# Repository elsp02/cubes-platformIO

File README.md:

# Modular Mechatronic Smart-Brick System for Tangible Learning in Special Education
Repository accompanying the Bachelor thesis:

**Design and Development of a Tangible Learning System for Special Education**

Elena Spitzer  
University of Applied Sciences Augsburg  
Faculty of Electrical Engineering  
Creative Engineering  
2026  

## Overview
This repository contains the prototype developed as part of the Bachelor thesis and investigates a modular, brick-based tangible learning game that combines the haptic and spatial qualities of physical construction materials with digital task presentation, construction detection and feedback. Learners select a three-dimensional target structure in a browser-based application and reproduce it using electronically connected building bricks. The system was designed to create opportunities for spatial thinking, action planning, problem-solving and increasingly independent learning while allowing task complexity and assistance to be adapted to individual needs. 

The system consists of three main components:

- **Active building bricks** that form the physical construction
- **A baseplate** that serves as the root of the construction
- **A learning application** that reconstructs the detected construction digitally

<center>

</center>

## Repository Structure

```text
.
├── README.md
│
├── docs/
│   ├── architecture.md
│   ├── communication-protocol.md
│   ├── feedback.md
│   ├── hardware.md
│   ├── language_c.md
│
├── figures/
│
├── firmware/
│   ├── include/
│   └── src/
│        ├── lib/
│        ├── firmware_test/
│        └── state_machine/
│         ├── baseplate_state_machine_debug.cpp
│         ├── baseplate_state_machine2.cpp
│         └── cube_state_machine.cpp
│
├── software/
│   └── threejs_visualization/
│     ├── backend/
│     └── frontend/
│
└── hardware/
    ├── pcb_files/
    └── CAD_files/

```

|Directory | Description |
|:--|:--|
| `docs/` | Technical documentation of the developed system |
| `firmware/` | Embedded firmware for the building bricks and the baseplate |
| `software/threejs_visualization/backend` | Python backend for communication and construction processing |
| `software/threejs_visualization/frontend` | Browser-based learning application and 3D visualisation |
| `hardware` | Electronic and mechanical design files

## Documentation
Detailed technical documentation is provided separately: 
- [System Architecuture](docs/system_architecture.md): Overall system structure, component responsibilities, software architecture and data processing
- [Communication Protocol](docs/communication_protocol.md): Communication interfaces, message formats, communication sequences (and error and timeout handling)
- [Hardware](docs/hardware.md): Mechanical and electronic implementation of the building bricks and baseplate

Addtional information regarding the feedback output and visualisation is provided in [Feedback and Visualisation](docs/feedback.md).

Firmware and Software Folders do also have additional README files [Firmware README](firmware/README.md), [Software README](software/README.md), as well as the backend [backend README](software/threejs_visualization/backend/README.md) 
and the frontend [frontend README](software/threejs_visualization/frontend/README.md)

(Furthermore, the bachelor thesis includes the complete design rationale, theoretical background, requirement analysis, implementation details and evaluation.)

## Requirements
to operate the complete physical prototype, the following hard- and software is required:

### Prototype Hardware
The building bricks and baseplate both include an ATtiny1616 and are custom developed components. Their mechanical and electronic design files are included in this repository in the [hardware](hardware/) and explained in [Hardware](docs/hardware.md)

### Additional Hardware
- 2× USB-to-TTL UART adapter (CH340/CH340G-based)
  - one modified with a TX/RX diode, used as UPDI programmer (jtag2updi)
  - one unmodified, used for host–baseplate UART communication and 5V supply
- host computer
- USB connection for 5V power supply

The prototype was programmed using the jtag2updi-compatible programmer.
Setup instructions are available in the
[jtag2updi documentation](https://github.com/SpenceKonde/AVR-Guidance/blob/master/UPDI/jtag2updi.md).

### Software
- [PlatformIO](https://platformio.org/)
- [megaTinyCore](https://github.com/SpenceKonde/megaTinyCore) for ATtiny1616 support
- Python 3.14
- modern web browser

**Python dependencies**:  
- `pyserial` (UART communication, [binary_serial_reader.py](software/threejs_visualization/backend/binary_serial_reader.py))
- `websockets` (backend WebSocket server, [ws_server.py](software/threejs_visualization/backend/ws_server.py))

Python dependencies can be installed via:  
```bash
pip install -r software/threejs_visualization/backend/requirements_backend.txt
```

**Frontend dependencies** (in [software/threejs_visualization/frontend/package.json](software/threejs_visualization/frontend/package.json)):  
- `three` (^0.185.1)  
- `vite` (^8.1.2) — dev server / bundler

Install with:  
```bash
cd software/threejs_visualization/frontend
npm install
```

## Getting Started
### 1. Clone the Repository
git `clone https://github.com/elsp02/cubes-platformIO.git`  
cd cubes-platformIO

### 2. Flash the Brick and Baseplate Firmware
for flashing use the modified USB-to-TTL UART adapter

#### Brick Firmware
the brick firmware is located in: [firmware/src/state_machine]  
Compile the firmware and upload the ATtiny1616 using PlatformIO:  
```bash
pio run -e [uart_cube_state_machine]
```

```bash
pio run -e [uart_cube_state_machine] -t upload
```
---
#### Baseplate Firmware
the baseplate firmware is located in: [firmware/src/state_machine]

Compile the firmware and upload the ATtiny1616 using PlatformIO: 
```bash
pio run -e [uart_baseplate_state_machine]
```

```bash
pio run -e [uart_baseplate_state_machine] -t upload
```
---
#### Debugging
 to run the baseplate standalone without a PC connection, cycling the predefined feedback patterns instead of PC-supplied data, flash the `[baseplate_state_machine_debug]` environment instead:
 ```bash
 pio run -e [baseplate_state_machine_debug]
 ```

### 3. Connect the Prototype
1. Connect the baseplate to the host computer using the unmodified USB-to-TTL UART adapter
2. ensure that the system is supplied with 5V
3. Do not connect bricks to the baseplate yet
For details about the physical and electronic interfaces, see the [Hardware Documentation](docs/hardware.md)

### 4. Start the Backend
Navigate to the backend directory:  
```bash
cd software/threejs_visualization/backend
```
Start the backend:
```bash
python ws_server.py
```

### 5. Start the Frontend
Navigate to the frontend directory:
```bash
cd software/threejs_visualization/frontend
```
Start the frontend and open it in a web browser:
```bash
npm run dev
```

## Usage
A typical construction task follows this sequence:
1. Start the backend and frontend
2. Select a target construction in the learning application
3. Inspect and confirm the selected three-dimensional target
4. Connect the first brick to the baseplate.
5. Continue the building process by trying to reproduce the target structure 
5. The system processes the current construction and updates the digital representation.
6. Rearrange a brick if it is detected and visualised as incorrect
7. Continue modifying the construction until the task is completed
8. End the current session or return to the target selection

The visualised feedback during the construction task inlcuding pyhsical and digital feedback and feedback states is explained in detail in the[Feedback Documentation](docs/feedback.md).

## Prototype Status
//baseplate flashed currently with uart_baseplate_sate_machine env of commit 9cc54fb7
//cube flashed currently with uart_cube_state_machine env of commit 05d4e983

This repository contains the proof-of-concept prototype developed for the Bachelor thesis. It is not a production-ready or certified educational product.

Further information about the evaluation, requirement fulfilment and limitations is provided in the Bachelor thesis.

## Version
The version associated with the submitted Bachelor thesis is:
Tag:    [prototype_v11_final]  
Commit: [FINAL_COMMIT]  

Later commits may contain modifications that are not described in the submitted thesis.

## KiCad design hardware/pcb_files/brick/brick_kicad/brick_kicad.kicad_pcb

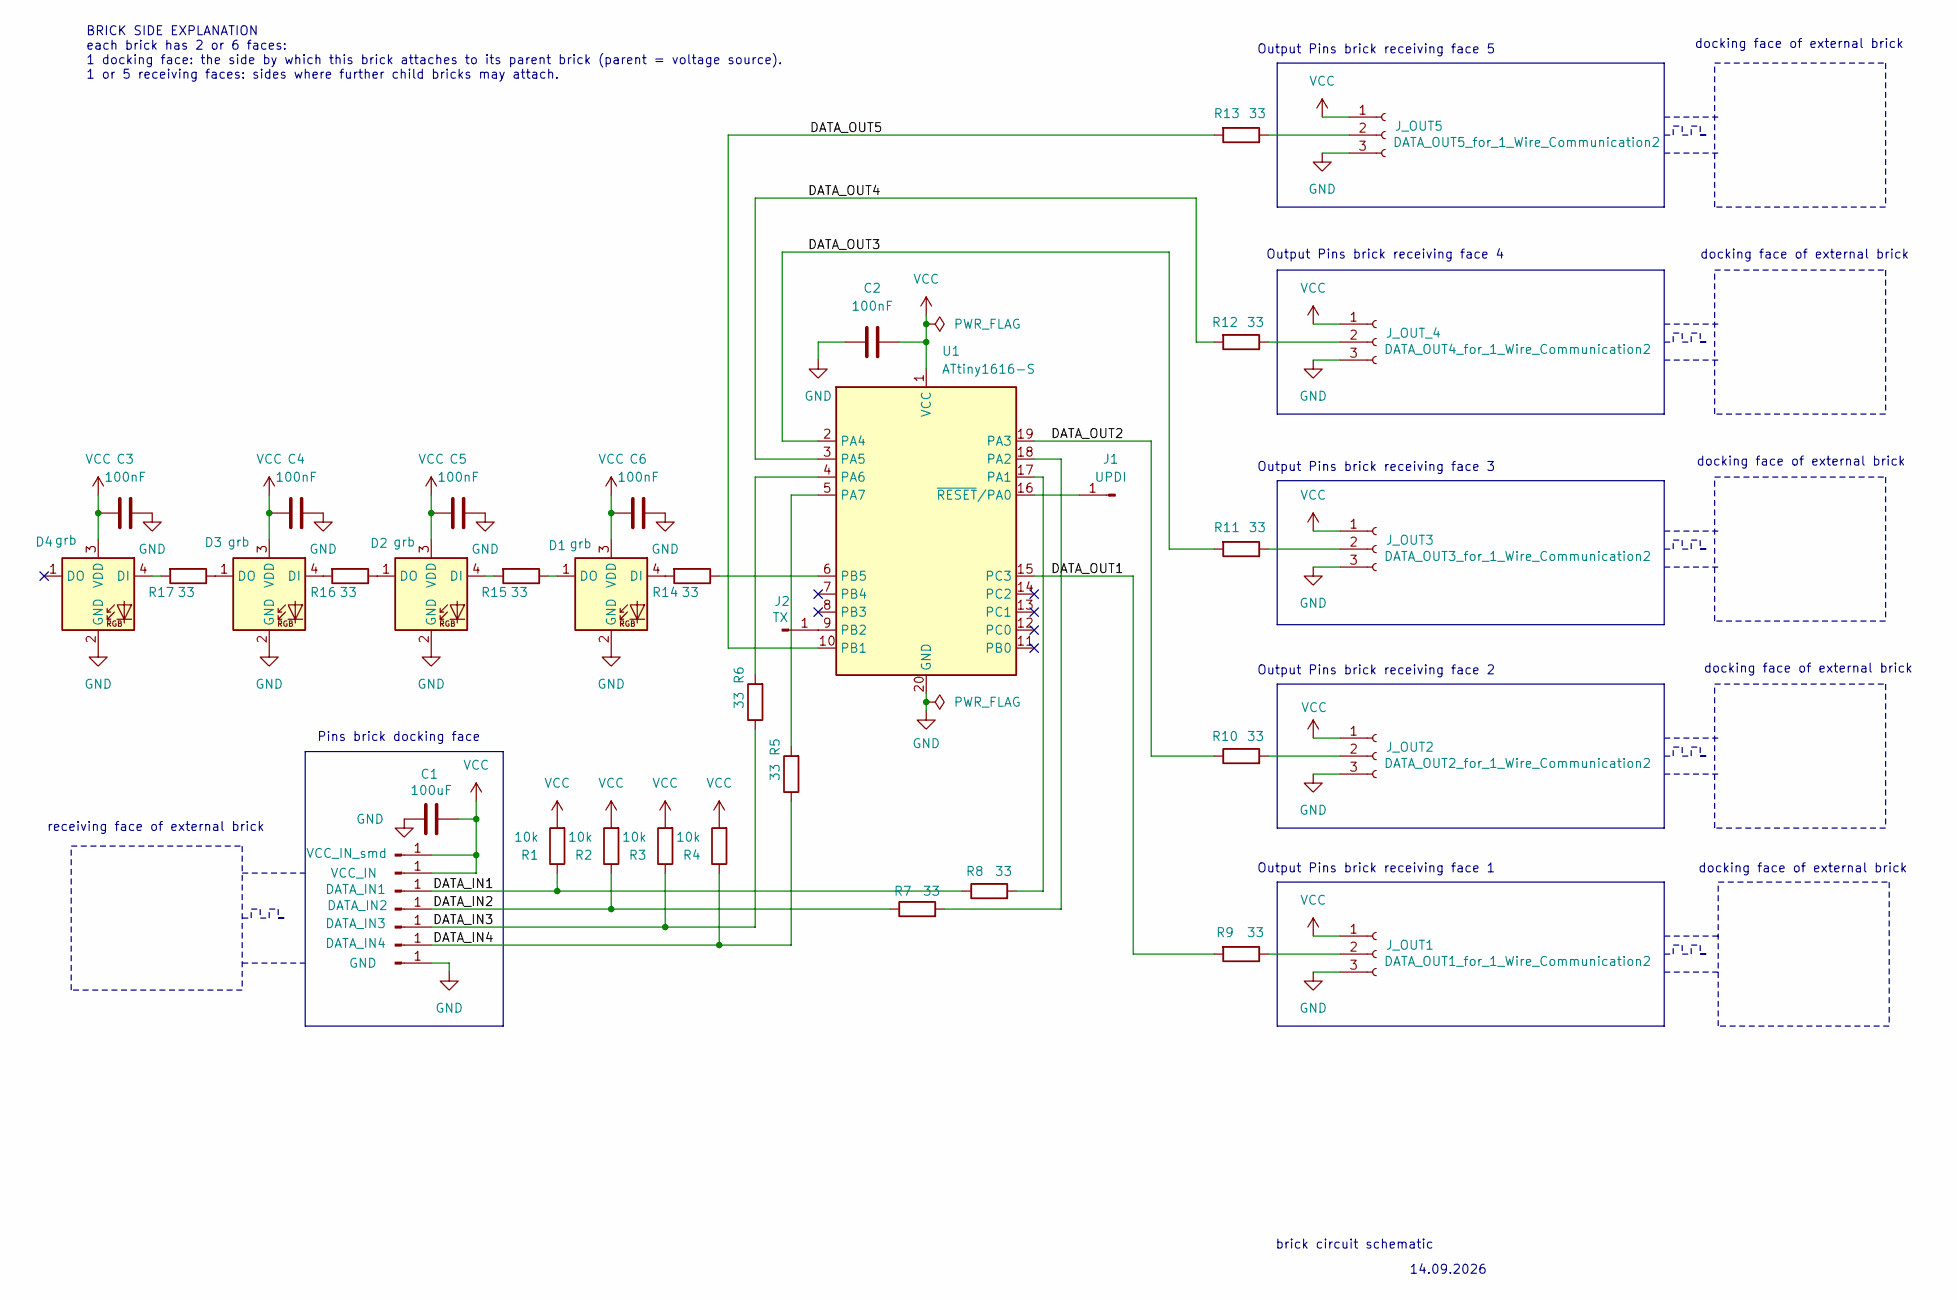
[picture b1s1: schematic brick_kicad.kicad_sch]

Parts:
C1: 100uF; C_1206_3216Metric_Pad1.33x1.80mm_HandSolder; MPN 885012108005
C2, C3, C4, C5, C6: 100nF; C_0805_2012Metric_Pad1.18x1.45mm_HandSolder; MPN 885012207016
D1, D2, D3, D4: grb; U_Wurth_WL-ICLED_1313210530000
J1: UPDI; PinSocket_1x01_P2.54mm_Vertical
J2: TX; PinSocket_1x01_P2.54mm_Vertical
J_GND1: GND; pogo_pad_IN
J_IN1: DATA_IN1; pogo_pad_IN
J_IN2: DATA_IN2; pogo_pad_IN
J_IN3: DATA_IN3; pogo_pad_IN
J_IN4: DATA_IN4; pogo_pad_IN
J_OUT1: DATA_OUT1_for_1_Wire_Communication2; Wuerth_WR-WTB_64800311622_1x03_P1.50mm_Vertical; MPN 64800311622
J_OUT2: DATA_OUT2_for_1_Wire_Communication2; Wuerth_WR-WTB_64800311622_1x03_P1.50mm_Vertical; MPN 64800311622
J_OUT3: DATA_OUT3_for_1_Wire_Communication2; Wuerth_WR-WTB_64800311622_1x03_P1.50mm_Vertical; MPN 64800311622
J_OUT5: DATA_OUT5_for_1_Wire_Communication2; Wuerth_WR-WTB_64800311622_1x03_P1.50mm_Vertical; MPN 64800311622
J_OUT_4: DATA_OUT4_for_1_Wire_Communication2; Wuerth_WR-WTB_64800311622_1x03_P1.50mm_Vertical; MPN 64800311622
J_VCC1: VCC_IN; pogo_pin_magnet
J_VCC2: VCC_IN_smd; pogo_pin_smd
R1, R2, R3, R4: 10k; R_0603_1608Metric_Pad0.98x0.95mm_HandSolder; MPN 560112116005
R5, R6, R7, R8, R9, R10, R11, R12, R13, R14, R15, R16, R17: 33; R_0603_1608Metric_Pad0.98x0.95mm_HandSolder; MPN 560112116034
U1: ATtiny1616-S; SOIC-20W_7.5x12.8mm_P1.27mm

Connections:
/DATA_IN1: J_IN1.1 (Pin_1_1), R1.1, R8.1
/DATA_IN2: J_IN2.1 (Pin_1_1), R2.1, R7.1
/DATA_IN3: J_IN3.1 (Pin_1_1), R3.1, R6.1
/DATA_IN4: J_IN4.1 (Pin_1_1), R4.1, R5.1
/DATA_OUT1: R9.2, U1.15 (PC3)
/DATA_OUT2: R10.1, U1.19 (PA3)
/DATA_OUT3: R11.2, U1.2 (PA4)
/DATA_OUT4: R12.2, U1.3 (PA5)
/DATA_OUT5: R13.2, U1.10 (PB1)
GND: C1.1, C2.2, C3.1, C4.1, C5.1, C6.1, D1.2 (GND), D2.2 (GND), D3.2 (GND), D4.2 (GND), J_GND1.1 (Pin_1_1), J_OUT1.3, J_OUT2.3, J_OUT3.3, J_OUT5.3, J_OUT_4.3, U1.20 (GND)
unnamed: D1.4 (DI), R14.2
unnamed: D1.1 (DO), R15.1
unnamed: D2.4 (DI), R15.2
unnamed: D2.1 (DO), R16.1
unnamed: D3.4 (DI), R16.2
unnamed: D3.1 (DO), R17.1
unnamed: D4.4 (DI), R17.2
unnamed: J1.1 (Pin_1_1), U1.16 (~RESET/PA0)
unnamed: J2.1 (Pin_1_1), U1.9 (PB2)
unnamed: J_OUT1.2, R9.1
unnamed: J_OUT2.2, R10.2
unnamed: J_OUT3.2, R11.1
unnamed: J_OUT5.2, R13.1
unnamed: J_OUT_4.2, R12.1
unnamed: R8.2, U1.17 (PA1)
unnamed: R7.2, U1.18 (PA2)
unnamed: R6.2, U1.4 (PA6)
unnamed: R5.2, U1.5 (PA7)
unnamed: R14.1, U1.6 (PB5)
VCC: C1.2, C2.1, C3.2, C4.2, C5.2, C6.2, D1.3 (VDD), D2.3 (VDD), D3.3 (VDD), D4.3 (VDD), J_OUT1.1, J_OUT2.1, J_OUT3.1, J_OUT5.1, J_OUT_4.1, J_VCC1.1 (Pin_1_1), J_VCC2.1 (Pin_1_1), R1.2, R2.2, R3.2, R4.2, U1.1 (VCC)

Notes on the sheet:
Output Pins brick receiving face 3
docking face of external brick
BRICK SIDE EXPLANATION each brick has 2 or 6 faces: 1 docking face: the side by which this brick attaches to its parent brick (parent = voltage source). 1 or 5 receiving faces: sides where further child bricks may attach.
14.09.2026
Output Pins brick receiving face 4
Output Pins brick receiving face 2
Output Pins brick receiving face 5
receiving face of external brick
Pins brick docking face
brick circuit schematic
Output Pins brick receiving face 1

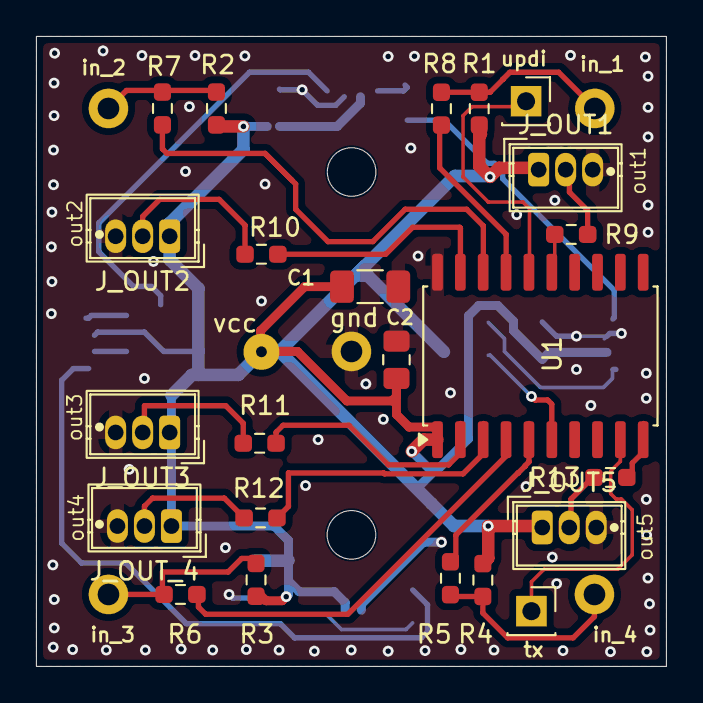
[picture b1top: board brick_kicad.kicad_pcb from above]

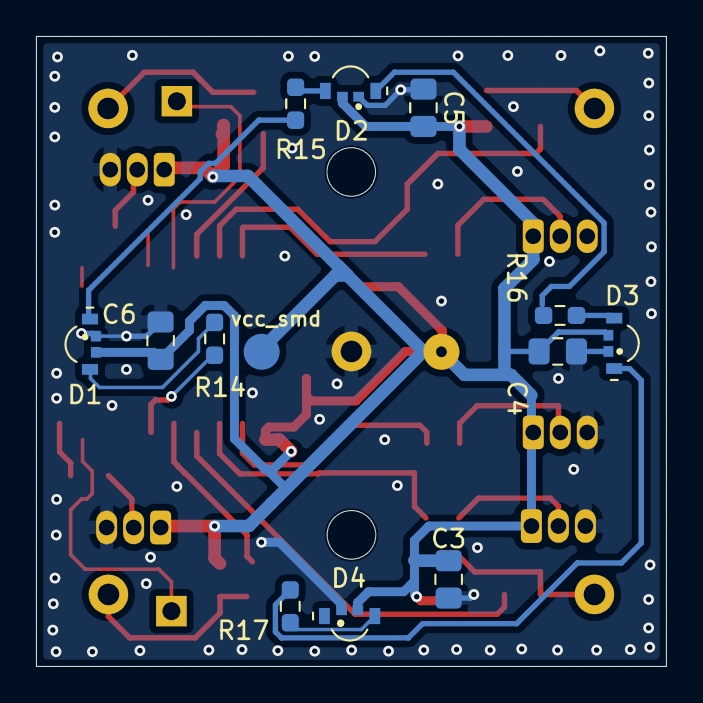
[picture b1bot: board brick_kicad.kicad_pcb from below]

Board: 2 copper layers, 35.0 x 35.0 mm, 42 parts (13 on the bottom side), 30 nets.

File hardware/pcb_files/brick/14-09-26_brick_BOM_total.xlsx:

Reference | Qty | Value | Footprint | Datasheet | Notes
C1 | 1 | 100uF | Capacitor_SMD:C_1206_3216Metric_Pad1.33x1.80mm_HandSolder
C2,C3,C4,C5,C6 | 5 | 100nF | Capacitor_SMD:C_0805_2012Metric_Pad1.18x1.45mm_HandSolder
D1,D2,D3,D4 | 4 | grb | ICLED_SMD_Wurth:U_Wurth_WL-ICLED_1313210530000 | https://www.we-online.com/components/products/datasheet/1313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
J1 | 1 | UPDI | Connector_PinSocket_2.54mm:PinSocket_1x01_P2.54mm_Vertical | https://www.we-online.com/components/products/datasheet/6130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
J2 | 1 | TX | Connector_PinSocket_2.54mm:PinSocket_1x01_P2.54mm_Vertical | https://www.we-online.com/components/products/datasheet/6130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
J_GND1 | 1 | GND | BA_footprint_Library:pogo_pad_IN | https://www.mouser.de/datasheet/3/6118/1/cpg_04_n_b.pdf | Ground (docking side)
J_IN1 | 1 | DATA_IN1 | BA_footprint_Library:pogo_pad_IN | https://www.mouser.de/datasheet/3/6118/1/cpg_04_n_b.pdf | female pogo pin: upstream orientation contact (docking face)
J_IN2 | 1 | DATA_IN2 | BA_footprint_Library:pogo_pad_IN | https://www.mouser.de/datasheet/3/6118/1/cpg_04_n_b.pdf | female pogo pin: upstream orientation contact (docking face)
J_IN3 | 1 | DATA_IN3 | BA_footprint_Library:pogo_pad_IN | https://www.mouser.de/datasheet/3/6118/1/cpg_04_n_b.pdf | female pogo pin: upstream orientation contact (docking face)
J_IN4 | 1 | DATA_IN4 | BA_footprint_Library:pogo_pad_IN | https://www.mouser.de/datasheet/3/6118/1/cpg_04_n_b.pdf | female pogo pin: upstream orientation contact (docking face)
J_OUT1 | 1 | DATA_OUT1_for_1_Wire_Communication2 | BA_footprint_Library:Wuerth_WR-WTB_64800311622_1x03_P1.50mm_Vertical | https://www.we-online.com/components/products/datasheet/6480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 | pin header for VCC, Ground and downstream child contact (receiving face)
J_OUT2 | 1 | DATA_OUT2_for_1_Wire_Communication2 | BA_footprint_Library:Wuerth_WR-WTB_64800311622_1x03_P1.50mm_Vertical | https://www.we-online.com/components/products/datasheet/6480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 | pin header for VCC, Ground and downstream child contact (receiving face)
J_OUT3 | 1 | DATA_OUT3_for_1_Wire_Communication2 | BA_footprint_Library:Wuerth_WR-WTB_64800311622_1x03_P1.50mm_Vertical | https://www.we-online.com/components/products/datasheet/6480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 | pin header for VCC, Ground and downstream child contact (receiving face)
J_OUT5 | 1 | DATA_OUT5_for_1_Wire_Communication2 | BA_footprint_Library:Wuerth_WR-WTB_64800311622_1x03_P1.50mm_Vertical | https://www.we-online.com/components/products/datasheet/6480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 | pin header for VCC, Ground and downstream child contact (receiving face)
J_OUT_4 | 1 | DATA_OUT4_for_1_Wire_Communication2 | BA_footprint_Library:Wuerth_WR-WTB_64800311622_1x03_P1.50mm_Vertical | https://www.we-online.com/components/products/datasheet/6480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 | pin header for VCC, Ground and downstream child contact (receiving face)
J_VCC1 | 1 | VCC_IN | BA_footprint_Library:pogo_pin_magnet
J_VCC2 | 1 | VCC_IN_smd | BA_footprint_Library:pogo_pin_smd | https://www.mouser.de/datasheet/3/6118/1/cpg_64_smt_b.pdf
R1,R2,R3,R4 | 4 | 10k | Resistor_SMD:R_0603_1608Metric_Pad0.98x0.95mm_HandSolder
R5,R6,R7,R8,R9,R10,R11,R12,R13,R14,R15,R16,R17 | 13 | 33 | Resistor_SMD:R_0603_1608Metric_Pad0.98x0.95mm_HandSolder
not on pcb - solder cup pogo pin | 15 (3 when smashed type) |  |  | https://4donline.ihs.com/images/VipMasterIC/IC/MMMC/MMMC-S-A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 | solder cup pogo pin: for VCC, Ground and downstream child contact (receiving fa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
U1 | 1 | ATtiny1616-S | Package_SO:SOIC-20W_7.5x12.8mm_P1.27mm | http://ww1.microchip.com/downloads/en/DeviceDoc/ATtiny3216_A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
Reference | Qty | Value | Link
Magnet docking face | 4 | Neodymium Disc D.4X2mm N48 | supermagneticshop
Magnet receiving face | 20 (4 when smashed type) | Neodymium Disc D.3X2mm N48 | supermagneticshop
Ring magnet for vcc construction | 2 | Neodymium Ring D.8X5X2mm | supermagneticshop
washer for vcc construction | 1 | Washer DIN 125 ?x1.5mm

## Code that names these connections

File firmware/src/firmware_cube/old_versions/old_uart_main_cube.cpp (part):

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// Upstream orientation ports.
// Index in this array equals orientation value.
static const wire_t upstream[] = {
    { &PORTA, PIN1_bm, 1 },     // PA1 — orientation 0
    { &PORTA, PIN2_bm, 2 },     // PA3 — orientation 1
    { &PORTA, PIN6_bm, 6 },     // PA4 — orientation 2
    { &PORTA, PIN7_bm, 7 },     // PA5 — orientation 3
};

//suggestion: replace UPSTREAM_COUNT with upstream_count to avoid hardcoding the count
static int upstream_count = sizeof(upstream) / sizeof(upstream[0]);

static const wire_t child_0 = { &PORTC, PIN3_bm, 3 };  // PC3 — child port 0
static const wire_t child_1 = { &PORTA, PIN3_bm, 3 };  // PA3 — child port 1
static const wire_t child_2 = { &PORTA, PIN4_bm, 4 };  // PA4 — child port 2
static const wire_t child_3 = { &PORTA, PIN5_bm, 5 };  // PA5 — child port 3
static const wire_t child_4 = { &PORTB, PIN1_bm, 1 };  // PB1 — child port 4

static const wire_t *children[CHILD_COUNT] = {
    &child_0,
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
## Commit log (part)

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2026-06-02 file directory changed
2026-06-04 prototype_v2 final
2026-06-04 definition prototype_v3
2026-06-04 changing structure and adding different env to .ini
2026-06-05 changing code to v_3 idea
2026-06-07 descriptions added
2026-06-07 renaming files
2026-06-07 Initial empty main
2026-06-07 Add README with project overview and structure
2026-06-08 adding main_cube_v3 and improving main_cube and main_cube_v2
2026-06-09 .ini env changed
2026-06-10 code for parser added
2026-06-11 parser and baseplate code added
2026-06-11 payload blob test added
2026-06-12 definition.txt changed
2026-06-13 Claude generated doc
2026-06-13 working payload blob test
2026-06-13 payload blob test added and definition updated
2026-06-13 vorzeitiger commit
2026-06-14 successful payload-vizualize transfer with env serial_writing_test
2026-06-14 faulty real payload vizualisation transfer over serial - wrong time synchronization of timeouts
2026-06-15 new directory structureand doc files but content still in progress
2026-06-15 documentation system, hardware, communication protocoll - not good
2026-06-27 wavedom diagrams and timing definition
2026-06-27 directory structure changed + timing definitions
2026-06-28 vorläufig
2026-06-28 vorläufig 2
2026-06-29 desynchronized sequences
2026-06-30 V4 IS CURRENTLY NOT WORKING BECAUSE OF DESYNCHRONIZATION - THEREFORE GO TO V2_2 or V5
2026-06-30 tidy v5 but no actualized code yet
2026-06-30 code of prototype_v2.2 +meshcat visualization added
